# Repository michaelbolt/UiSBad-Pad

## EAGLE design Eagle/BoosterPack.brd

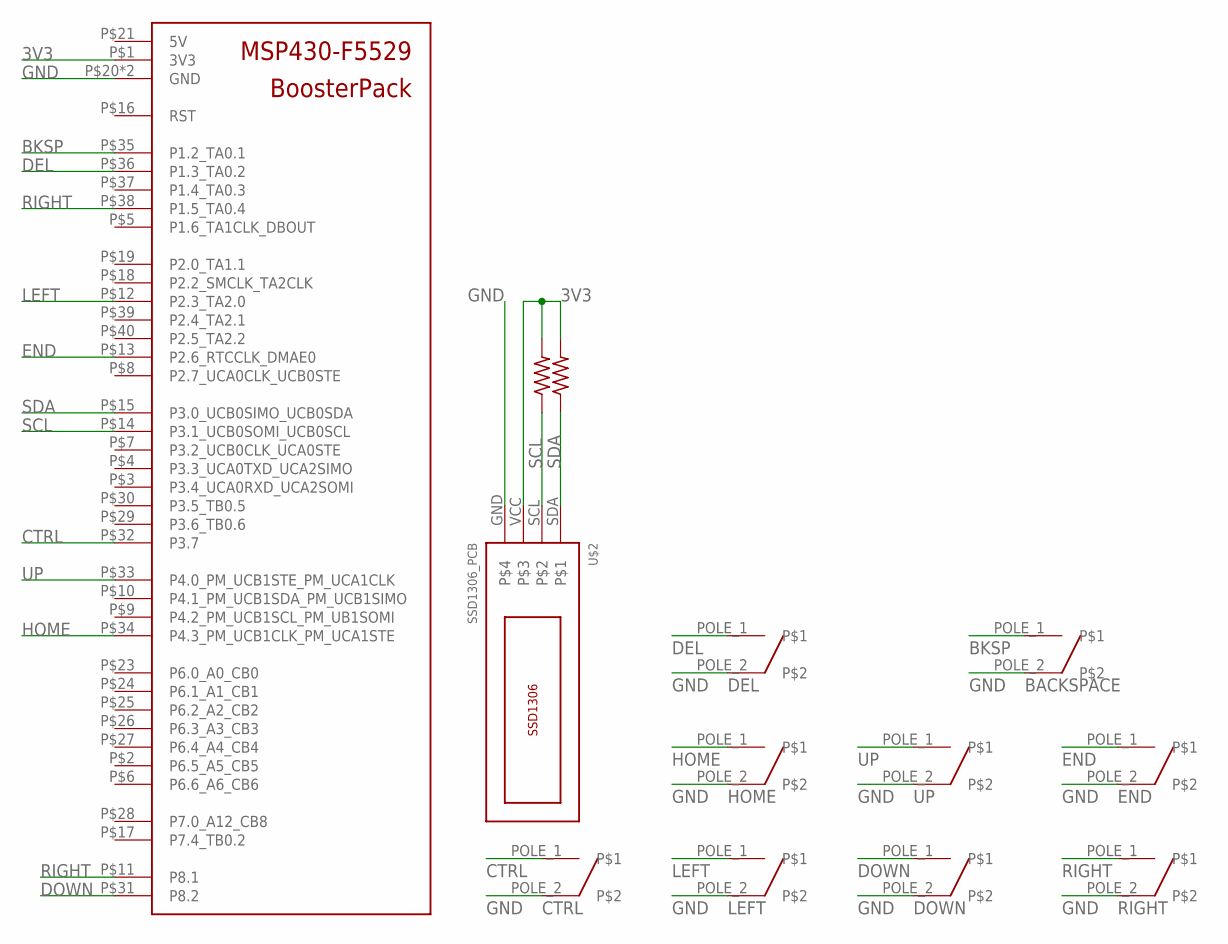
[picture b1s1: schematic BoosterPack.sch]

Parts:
BACKSPACE: CHERRY_MX
CTRL: CHERRY_MX
DEL: CHERRY_MX
DOWN: CHERRY_MX
END: CHERRY_MX
HOME: CHERRY_MX
LEFT: CHERRY_MX
R1, R2: R-US_0207/10; 0207/10
RIGHT: CHERRY_MX
U$1: MSP430_F5529_BOOSTERPACK; LAUNCHPAD_40PIN
U$2: SSD1306_PCB
UP: CHERRY_MX

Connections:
3V3: R1.2, R2.2, U$1.P$1 (3V3), U$2.VCC
BKSP: BACKSPACE.POLE_1, U$1.P$35 (P1.2_TA0.1)
CTRL: CTRL.POLE_1, U$1.P$32 (P3.7)
DEL: DEL.POLE_1, U$1.P$36 (P1.3_TA0.2)
DOWN: DOWN.POLE_1, U$1.P$31 (P8.2)
END: END.POLE_1, U$1.P$13 (P2.6_RTCCLK_DMAE0)
GND: BACKSPACE.POLE_2, CTRL.POLE_2, DEL.POLE_2, DOWN.POLE_2, END.POLE_2, HOME.POLE_2, LEFT.POLE_2, RIGHT.POLE_2, U$1.P$20 (GND), U$1.P$22 (GND), U$2.GND, UP.POLE_2
HOME: HOME.POLE_1, U$1.P$34 (P4.3_PM_UCB1CLK_PM_UCA1STE)
LEFT: LEFT.POLE_1, U$1.P$12 (P2.3_TA2.0)
RIGHT: RIGHT.POLE_1, U$1.P$11 (P8.1), U$1.P$38 (P1.5_TA0.4)
SCL: R2.1, U$1.P$14 (P3.1_UCB0SOMI_UCB0SCL), U$2.SCL
SDA: R1.1, U$1.P$15 (P3.0_UCB0SIMO_UCB0SDA), U$2.SDA
UP: U$1.P$33 (P4.0_PM_UCB1STE_PM_UCA1CLK), UP.POLE_1

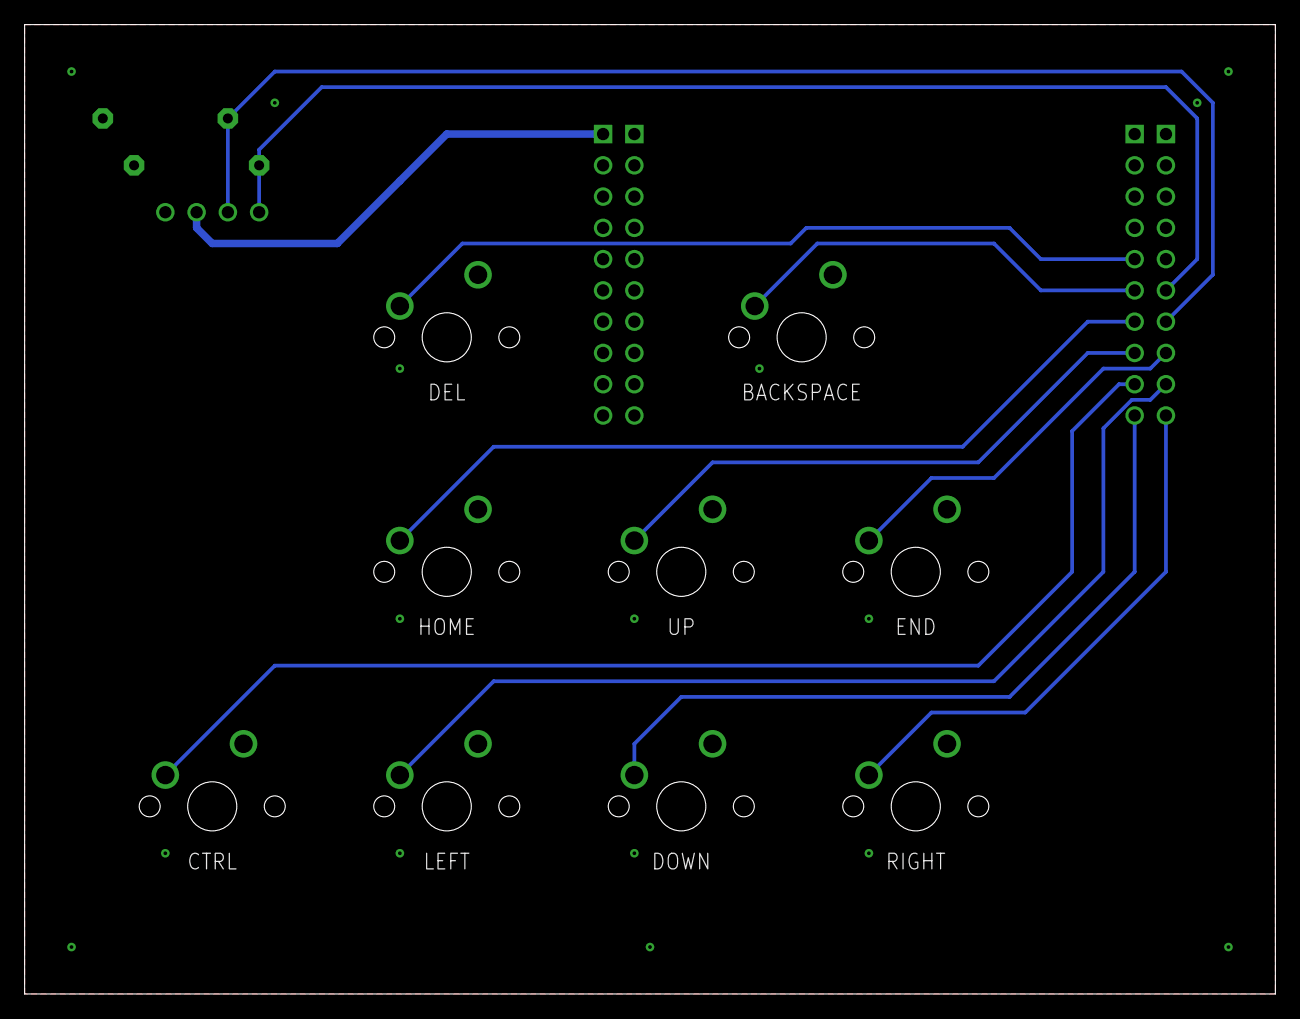
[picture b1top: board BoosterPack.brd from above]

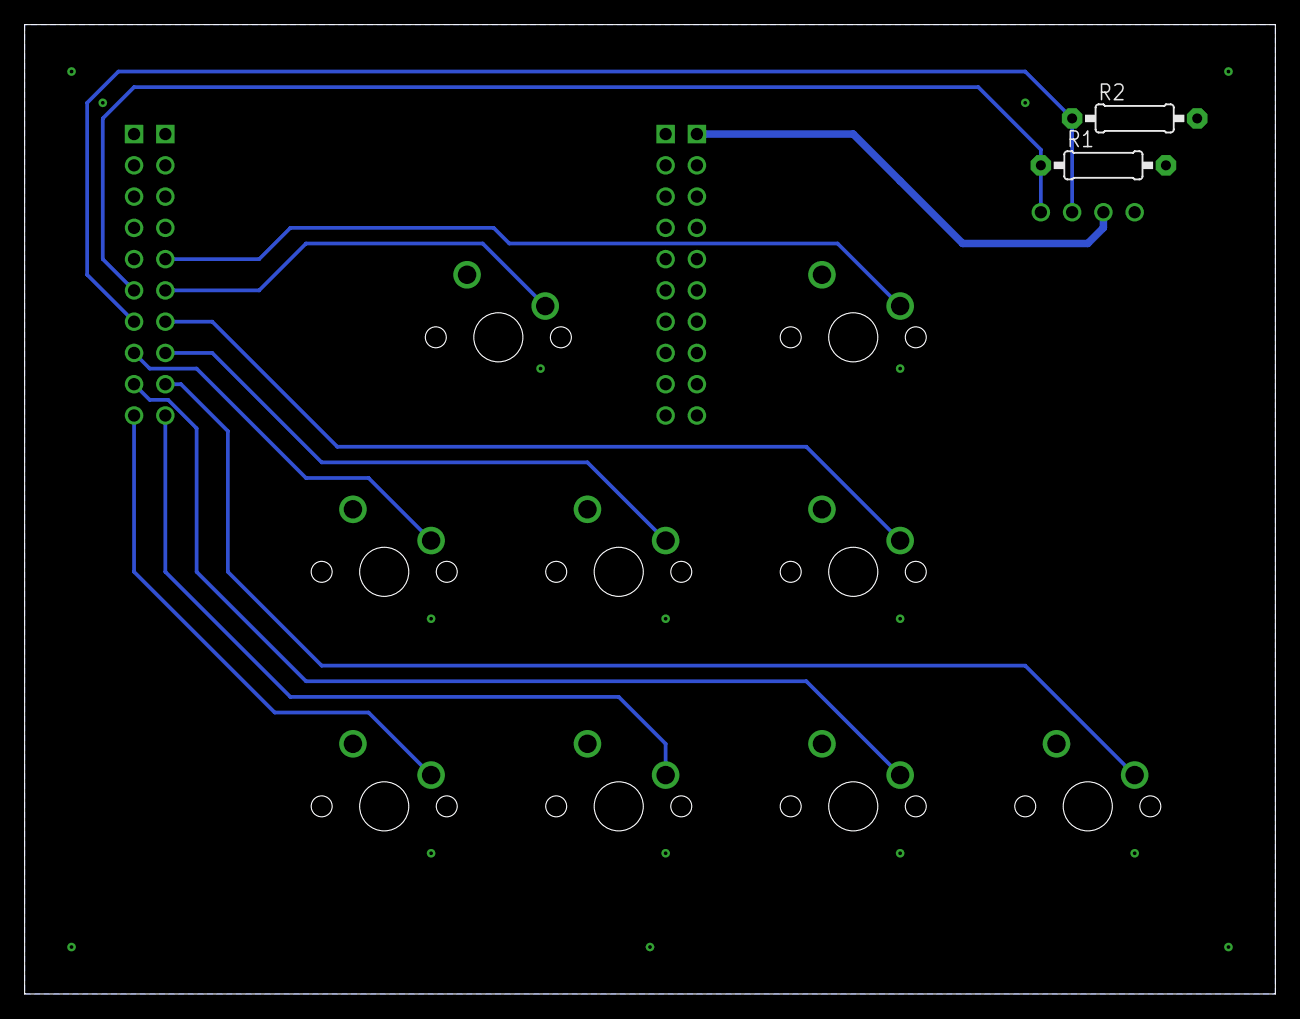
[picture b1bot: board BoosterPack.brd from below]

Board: 2 copper layers, 101.6 x 78.7 mm, 13 parts (2 on the bottom side), 13 nets.

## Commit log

2020-12-20 BoosterPack Prototype
    Ordered a simple Boosterpack compatible pcb for development
2020-12-22 Added Drill file to Gerber
    I forgot to include the drill files in my Gerber .zip - Whoops!
